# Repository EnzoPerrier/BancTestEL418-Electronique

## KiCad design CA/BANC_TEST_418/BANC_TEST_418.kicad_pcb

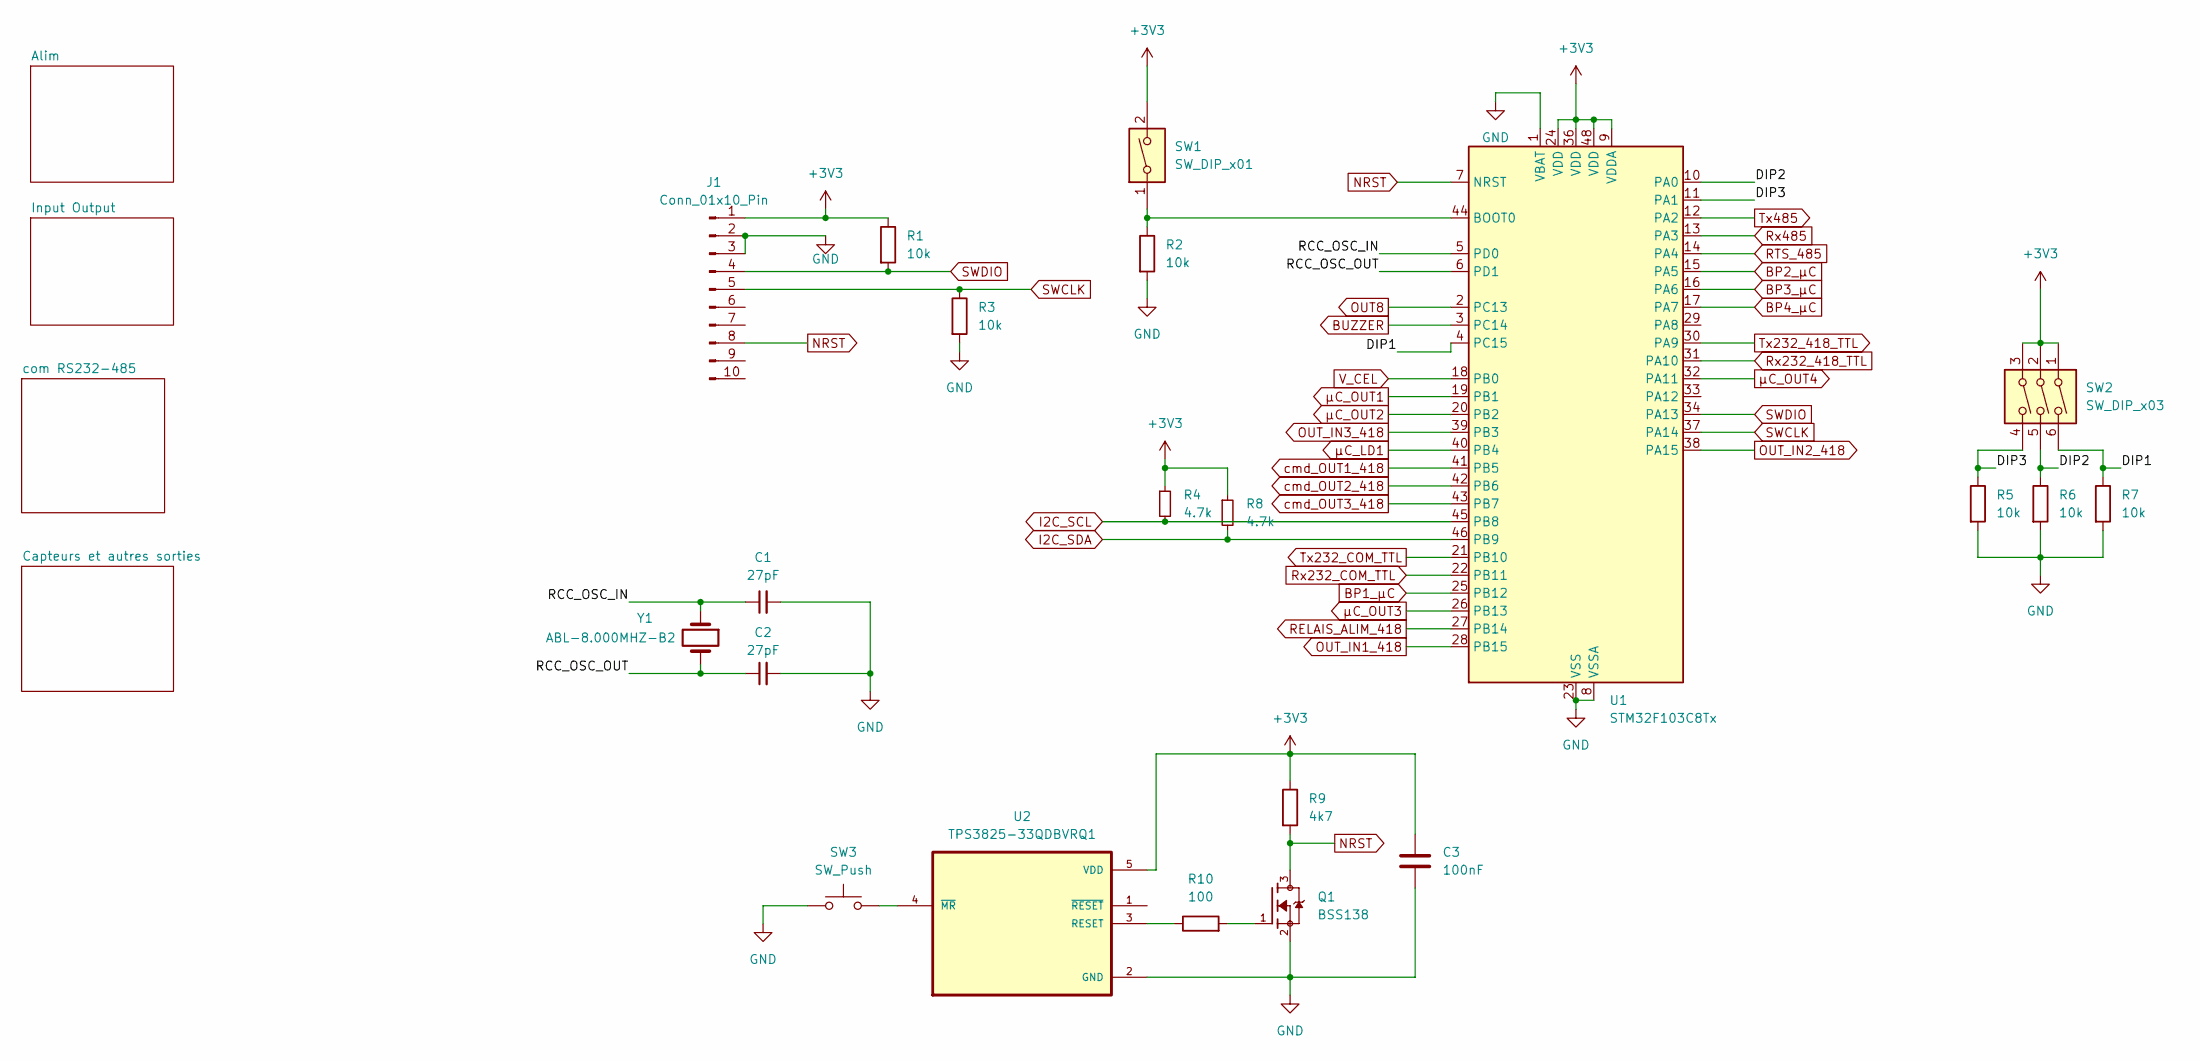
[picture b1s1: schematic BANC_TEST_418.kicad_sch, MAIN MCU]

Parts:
C1, C2: 27pF; C_0805_2012Metric_Pad1.18x1.45mm_HandSolder
C3: 100nF; C_0805_2012Metric_Pad1.18x1.45mm_HandSolder
J1: Conn_01x10_Pin; PinHeader_1x10_P2.54mm_Vertical
Q1: BSS138; SOT95P240X111-3N; PARTREV 30 Jan 2018
R1, R2, R3, R5, R6, R7: 10k; R_0805_2012Metric_Pad1.20x1.40mm_HandSolder
R4, R8: 4.7k; R_0805_2012Metric_Pad1.20x1.40mm_HandSolder
R9: 4k7; R_0805_2012Metric_Pad1.20x1.40mm_HandSolder
R10: 100; R_0805_2012Metric_Pad1.20x1.40mm_HandSolder
SW1: SW_DIP_x01; SW_DIP_SPSTx01_Slide_9.78x4.72mm_W8.61mm_P2.54mm
SW2: SW_DIP_x03; SW_DIP_SPSTx03_Slide_Omron_A6S-310x_W8.9mm_P2.54mm
SW3: SW_Push; SW_SPST_Omron_B3FS-100xP
U1: STM32F103C8Tx; LQFP-48_7x7mm_P0.5mm
U2: TPS3825-33QDBVRQ1; TPS3825-SOT95P280X145-5N
Y1: ABL-8.000MHZ-B2; Crystal_SMD_HC49-SD

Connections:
+3V3: C3.1, J1.1, R1.1, R4.1, R8.1, R9.1, SW1.2, SW2.1, SW2.2, SW2.3, U1.9 (VDDA), U1.24 (VDD), U1.36 (VDD), U1.48 (VDD), U2.5 (VDD); also elsewhere on the board
/DIP1: R7.1, SW2.6, U1.4 (PC15)
/DIP2: R6.1, SW2.5, U1.10 (PA0)
/DIP3: R5.1, SW2.4, U1.11 (PA1)
/RCC_OSC_IN: C1.1, U1.5 (PD0), Y1.1
/RCC_OSC_OUT: C2.1, U1.6 (PD1), Y1.2
BP1_µC: U1.25 (PB12); also elsewhere on the board
BP2_µC: U1.15 (PA5); also elsewhere on the board
BP3_µC: U1.16 (PA6); also elsewhere on the board
BP4_µC: U1.17 (PA7); also elsewhere on the board
BUZZER: U1.3 (PC14); also elsewhere on the board
GND: C1.2, C2.2, C3.2, J1.2, J1.3, Q1.2, R2.2, R3.2, R5.2, R6.2, R7.2, SW3.1, U1.1 (VBAT), U1.8 (VSSA), U1.23 (VSS), U1.35 (VSS), U1.47 (VSS), U2.2 (GND); also elsewhere on the board
I2C_SCL: R4.2, U1.45 (PB8); also elsewhere on the board
I2C_SDA: R8.2, U1.46 (PB9); also elsewhere on the board
NRST: J1.8, Q1.3, R9.2, U1.7 (NRST)
unnamed: Q1.1, R10.2
unnamed: R2.1, SW1.1, U1.44 (BOOT0)
unnamed: R10.1, U2.3 (RESET)
unnamed: SW3.2, U2.4 (~MR)
OUT8: U1.2 (PC13)
OUT_IN1_418: U1.28 (PB15); also elsewhere on the board
OUT_IN2_418: U1.38 (PA15); also elsewhere on the board
OUT_IN3_418: U1.39 (PB3); also elsewhere on the board
RELAIS_ALIM_418: U1.27 (PB14); also elsewhere on the board
RTS_485: U1.14 (PA4); also elsewhere on the board
Rx232_418_TTL: U1.31 (PA10); also elsewhere on the board
Rx232_COM_TTL: U1.22 (PB11); also elsewhere on the board
Rx485: U1.13 (PA3); also elsewhere on the board
SWCLK: J1.5, R3.1, U1.37 (PA14)
SWDIO: J1.4, R1.2, U1.34 (PA13)
Tx232_418_TTL: U1.30 (PA9); also elsewhere on the board
Tx232_COM_TTL: U1.21 (PB10); also elsewhere on the board
Tx485: U1.12 (PA2); also elsewhere on the board
V_CEL: U1.18 (PB0); also elsewhere on the board
cmd_OUT1_418: U1.41 (PB5); also elsewhere on the board
cmd_OUT2_418: U1.42 (PB6); also elsewhere on the board
cmd_OUT3_418: U1.43 (PB7); also elsewhere on the board
µC_LD1: U1.40 (PB4); also elsewhere on the board
µC_OUT1: U1.19 (PB1); also elsewhere on the board
µC_OUT2: U1.20 (PB2); also elsewhere on the board
µC_OUT3: U1.26 (PB13); also elsewhere on the board
µC_OUT4: U1.32 (PA11); also elsewhere on the board

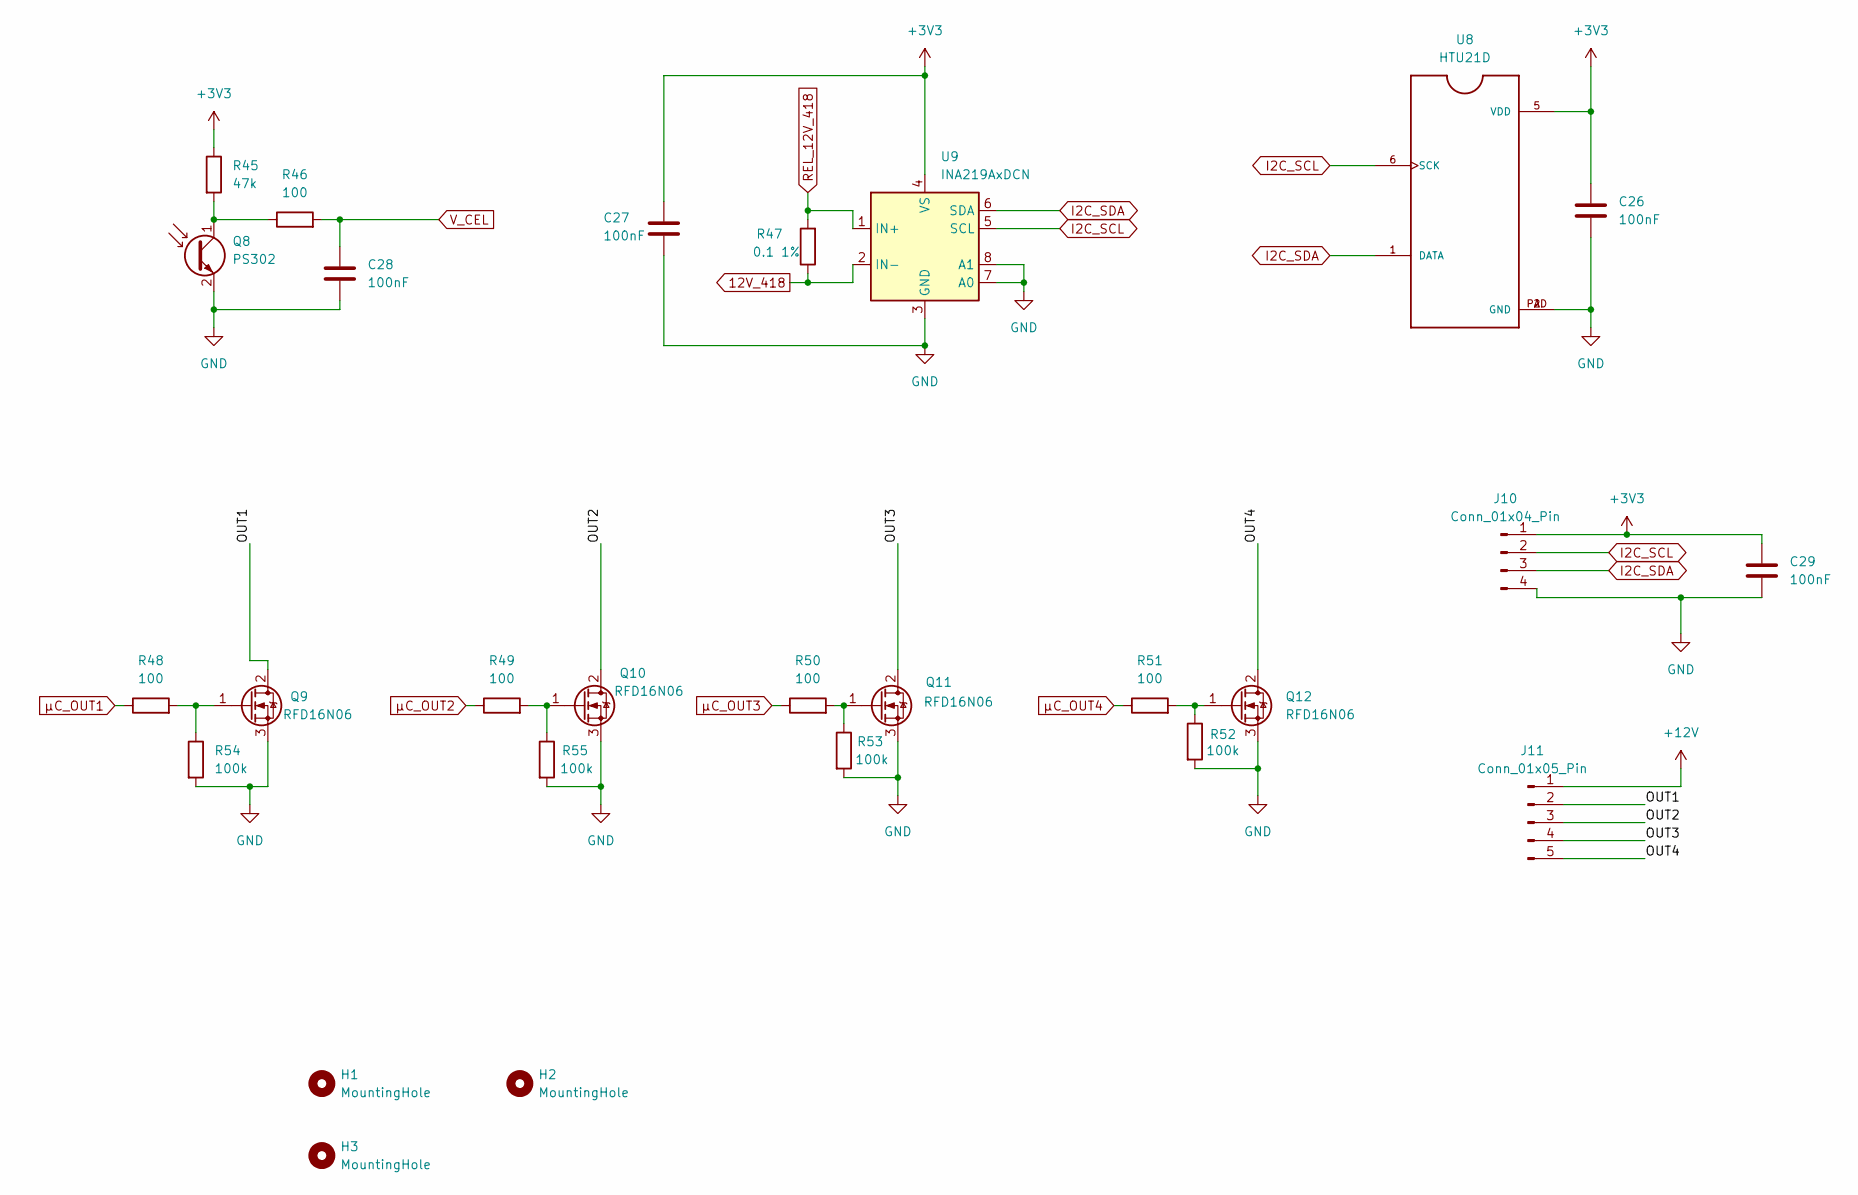
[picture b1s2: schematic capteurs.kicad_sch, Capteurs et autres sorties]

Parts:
C26, C27, C28, C29: 100nF; C_0805_2012Metric_Pad1.18x1.45mm_HandSolder
H1, H2, H3: MountingHole; MountingHole_4.3mm_M4_Pad
J10: Conn_01x04_Pin; NS-Tech_Grove_1x04_P2mm_Vertical
J11: Conn_01x05_Pin; PhoenixContact_MCV_1,5_5-G-3.81_1x05_P3.81mm_Vertical
Q8: PS302; LED_D5.0mm_Clear
Q9, Q10, Q11, Q12: RFD16N06; TO-252-2
R45: 47k; R_0805_2012Metric_Pad1.20x1.40mm_HandSolder
R46, R48, R49, R50, R51: 100; R_0805_2012Metric_Pad1.20x1.40mm_HandSolder
R47: 0.1 1%; R_2512_6332Metric_Pad1.40x3.35mm_HandSolder
R52, R53, R54, R55: 100k; R_0805_2012Metric_Pad1.20x1.40mm_HandSolder
U8: HTU21D; QFN100P300X300X100-7N
U9: INA219AxDCN; SOT-23-8

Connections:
12V_418: R47.1, U9.2 (IN-); also elsewhere on the board
+3V3: C26.1, C27.1, C29.1, J10.1, R45.1, U8.5 (VDD), U9.4 (VS); also elsewhere on the board
+12V: J11.1; also elsewhere on the board
/Capteurs et autres sorties/OUT1: J11.2, Q9.2 (D)
/Capteurs et autres sorties/OUT2: J11.3, Q10.2 (D)
/Capteurs et autres sorties/OUT3: J11.4, Q11.2 (D)
/Capteurs et autres sorties/OUT4: J11.5, Q12.2 (D)
GND: C26.2, C27.2, C28.2, C29.2, J10.4, Q8.2 (E), Q9.3 (S), Q10.3 (S), Q11.3 (S), Q12.3 (S), R52.2, R53.2, R54.2, R55.2, U8.2 (GND), U8.PAD (GND), U9.3 (GND), U9.7 (A0), U9.8 (A1); also elsewhere on the board
I2C_SCL: J10.2, U8.6 (SCK), U9.5 (SCL); also elsewhere on the board
I2C_SDA: J10.3, U8.1 (DATA), U9.6 (SDA); also elsewhere on the board
unnamed: Q8.1 (C), R45.2, R46.1
unnamed: Q9.1 (G), R48.2, R54.1
unnamed: Q10.1 (G), R49.2, R55.1
unnamed: Q11.1 (G), R50.2, R53.1
unnamed: Q12.1 (G), R51.2, R52.1
REL_12V_418: R47.2, U9.1 (IN+); also elsewhere on the board
V_CEL: C28.1, R46.2; also elsewhere on the board
µC_OUT1: R48.1; also elsewhere on the board
µC_OUT2: R49.1; also elsewhere on the board
µC_OUT3: R50.1; also elsewhere on the board
µC_OUT4: R51.1; also elsewhere on the board

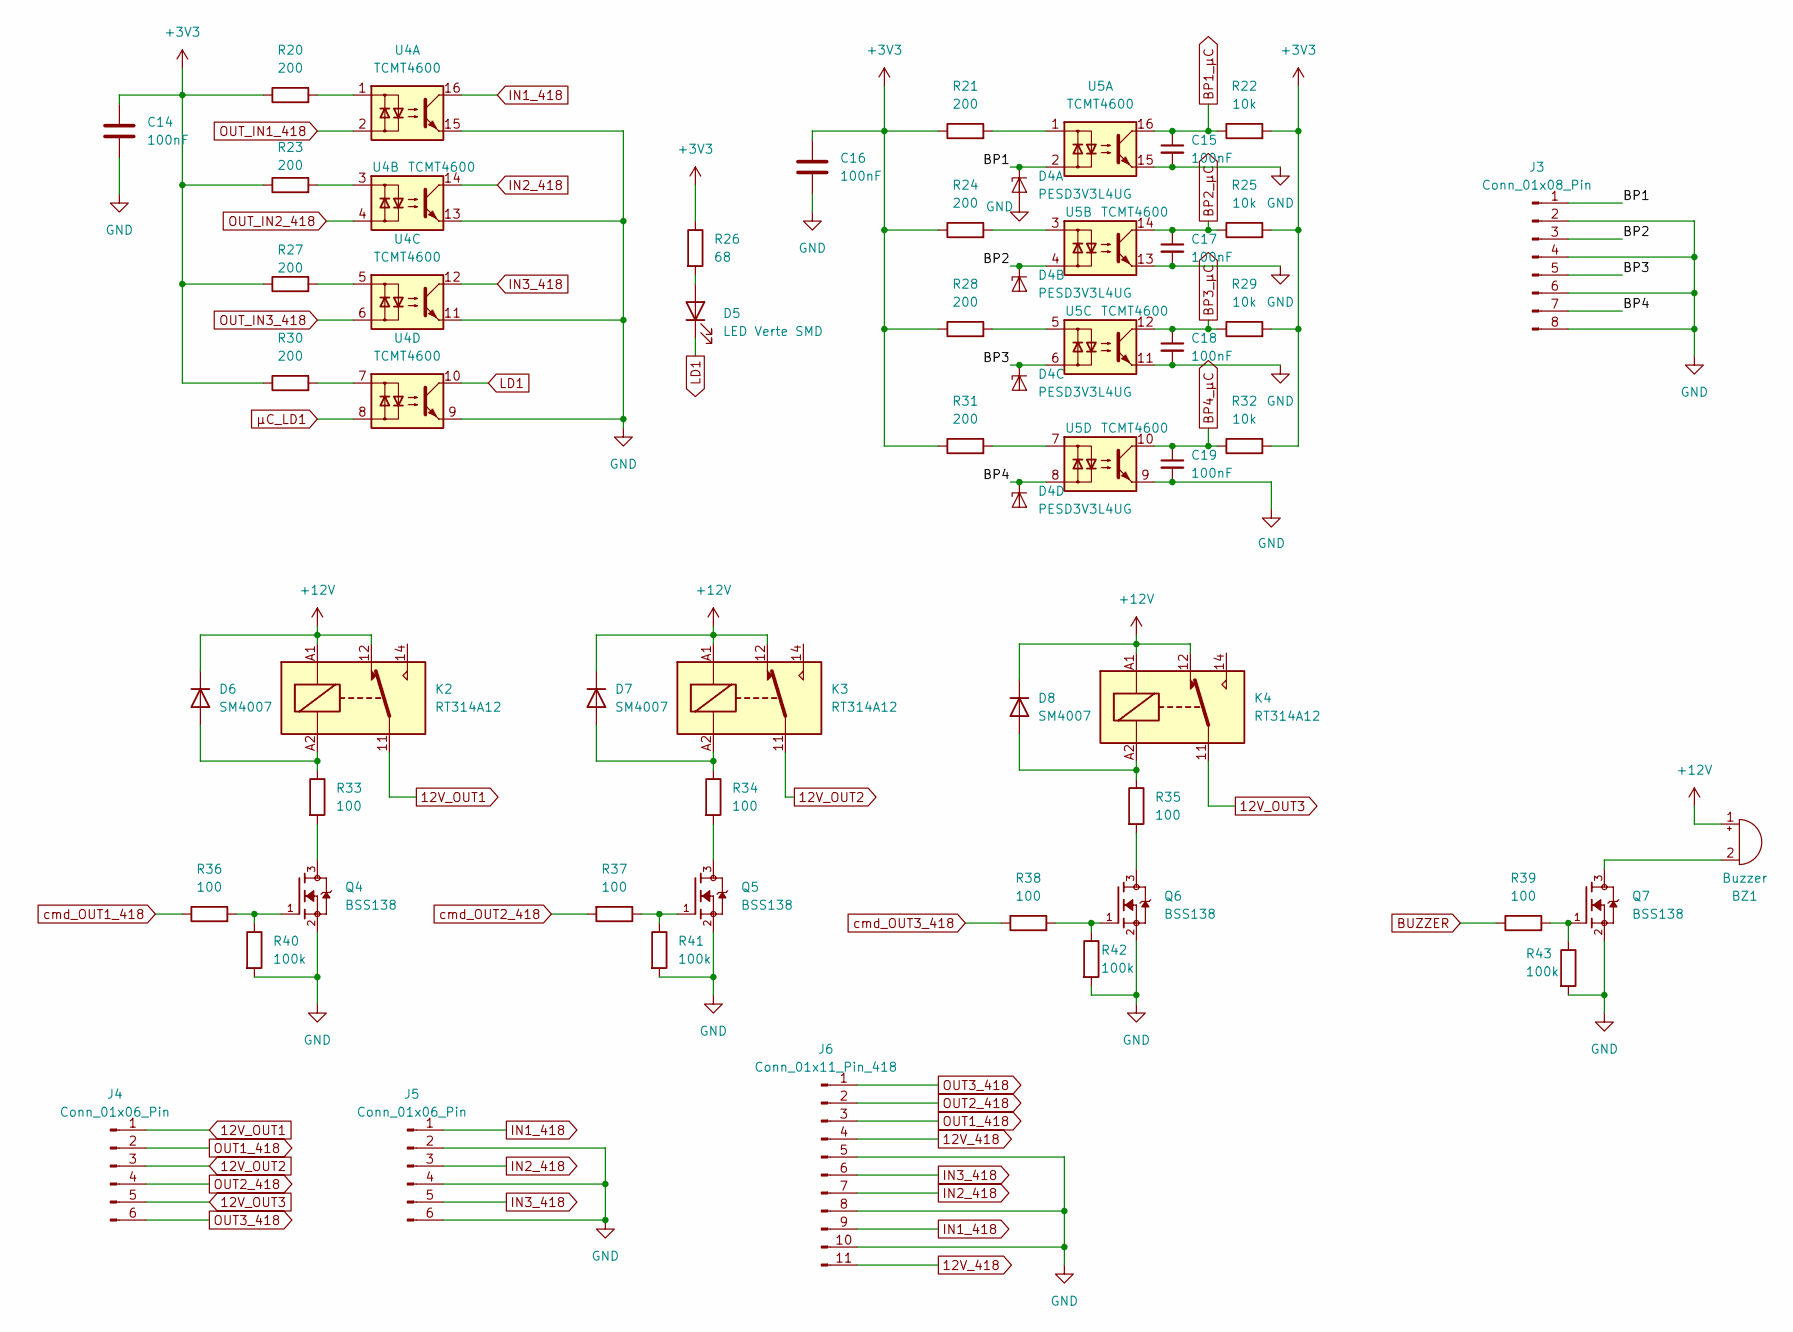
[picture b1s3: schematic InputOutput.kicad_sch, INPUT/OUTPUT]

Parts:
BZ1: Buzzer; Buzzer_15x7.5RM7.6
C14, C15, C16, C17, C18, C19: 100nF; C_0805_2012Metric_Pad1.18x1.45mm_HandSolder
D4: PESD3V3L4UG; SOT-353_SC-70-5
D5: LED Verte SMD; LED_0805_2012Metric_Pad1.15x1.40mm_HandSolder
D6, D7, D8: SM4007; D_MELF
J3: Conn_01x08_Pin; PhoenixContact_MCV_1,5_8-G-3.81_1x08_P3.81mm_Vertical
J4, J5: Conn_01x06_Pin; PhoenixContact_MCV_1,5_6-G-3.81_1x06_P3.81mm_Vertical
J6: Conn_01x11_Pin_418; PhoenixContact_MSTBVA_2,5_11-G-5,08_1x11_P5.08mm_Vertical
K2, K3, K4: RT314A12; Relay_SPDT_Schrack-RT1-16A-FormC_RM5mm
Q4, Q5, Q6, Q7: BSS138; SOT95P240X111-3N; PARTREV 30 Jan 2018
R20, R21, R23, R24, R27, R28, R30, R31: 200; R_0805_2012Metric_Pad1.20x1.40mm_HandSolder
R22, R25, R29, R32: 10k; R_0805_2012Metric_Pad1.20x1.40mm_HandSolder
R26: 68; R_0805_2012Metric_Pad1.20x1.40mm_HandSolder
R33, R34, R35, R36, R37, R38, R39: 100; R_0805_2012Metric_Pad1.20x1.40mm_HandSolder
R40, R41, R42, R43: 100k; R_0805_2012Metric_Pad1.20x1.40mm_HandSolder
U4, U5: TCMT4600; SOP-16_4.55x10.3mm_P1.27mm

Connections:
12V_418: J6.4, J6.11; also elsewhere on the board
12V_OUT1: J4.1, K2.11
12V_OUT2: J4.3, K3.11
12V_OUT3: J4.5, K4.11
+3V3: C14.1, C16.1, R20.1, R21.1, R22.2, R23.1, R24.1, R25.2, R26.1, R27.1, R28.1, R29.2, R30.1, R31.1, R32.2; also elsewhere on the board
+12V: BZ1.1 (+), D6.1 (K), D7.1 (K), D8.1 (K), K2.12, K2.A1, K3.12, K3.A1, K4.12, K4.A1; also elsewhere on the board
/Input Output/BP1: D4.1 (K1), J3.1, U5.2
/Input Output/BP2: D4.3 (K2), J3.3, U5.4
/Input Output/BP3: D4.4 (K3), J3.5, U5.6
/Input Output/BP4: D4.5 (K4), J3.7, U5.8
BP1_µC: C15.1, R22.1, U5.16; also elsewhere on the board
BP2_µC: C17.1, R25.1, U5.14; also elsewhere on the board
BP3_µC: C18.1, R29.1, U5.12; also elsewhere on the board
BP4_µC: C19.1, R32.1, U5.10; also elsewhere on the board
BUZZER: R39.1; also elsewhere on the board
GND: C14.2, C15.2, C16.2, C17.2, C18.2, C19.2, D4.2 (A), J3.2, J3.4, J3.6, J3.8, J5.2, J5.4, J5.6, J6.5, J6.8, J6.10, Q4.2, Q5.2, Q6.2, Q7.2, R40.2, R41.2, R42.2, R43.2, U4.9, U4.11, U4.13, U4.15, U5.9, U5.11, U5.13, U5.15; also elsewhere on the board
IN1_418: J5.1, J6.9, U4.16
IN2_418: J5.3, J6.7, U4.14
IN3_418: J5.5, J6.6, U4.12
LD1: D5.1 (K), U4.10
unnamed: BZ1.2 (-), Q7.3
unnamed: D5.2 (A), R26.2
unnamed: D6.2 (A), K2.A2, R33.1
unnamed: D7.2 (A), K3.A2, R34.1
unnamed: D8.2 (A), K4.A2, R35.1
unnamed: Q4.1, R36.2, R40.1
unnamed: Q4.3, R33.2
unnamed: Q5.1, R37.1, R41.1
unnamed: Q5.3, R34.2
unnamed: Q6.1, R38.2, R42.1
unnamed: Q6.3, R35.2
unnamed: Q7.1, R39.2, R43.1
unnamed: R20.2, U4.1
unnamed: R21.2, U5.1
unnamed: R23.2, U4.3
unnamed: R24.2, U5.3
unnamed: R27.2, U4.5
unnamed: R28.2, U5.5
unnamed: R30.2, U4.7
unnamed: R31.2, U5.7
OUT1_418: J4.2, J6.3
OUT2_418: J4.4, J6.2
OUT3_418: J4.6, J6.1
OUT_IN1_418: U4.2; also elsewhere on the board
OUT_IN2_418: U4.4; also elsewhere on the board
OUT_IN3_418: U4.6; also elsewhere on the board
cmd_OUT1_418: R36.1; also elsewhere on the board
cmd_OUT2_418: R37.2; also elsewhere on the board
cmd_OUT3_418: R38.1; also elsewhere on the board
µC_LD1: U4.8; also elsewhere on the board

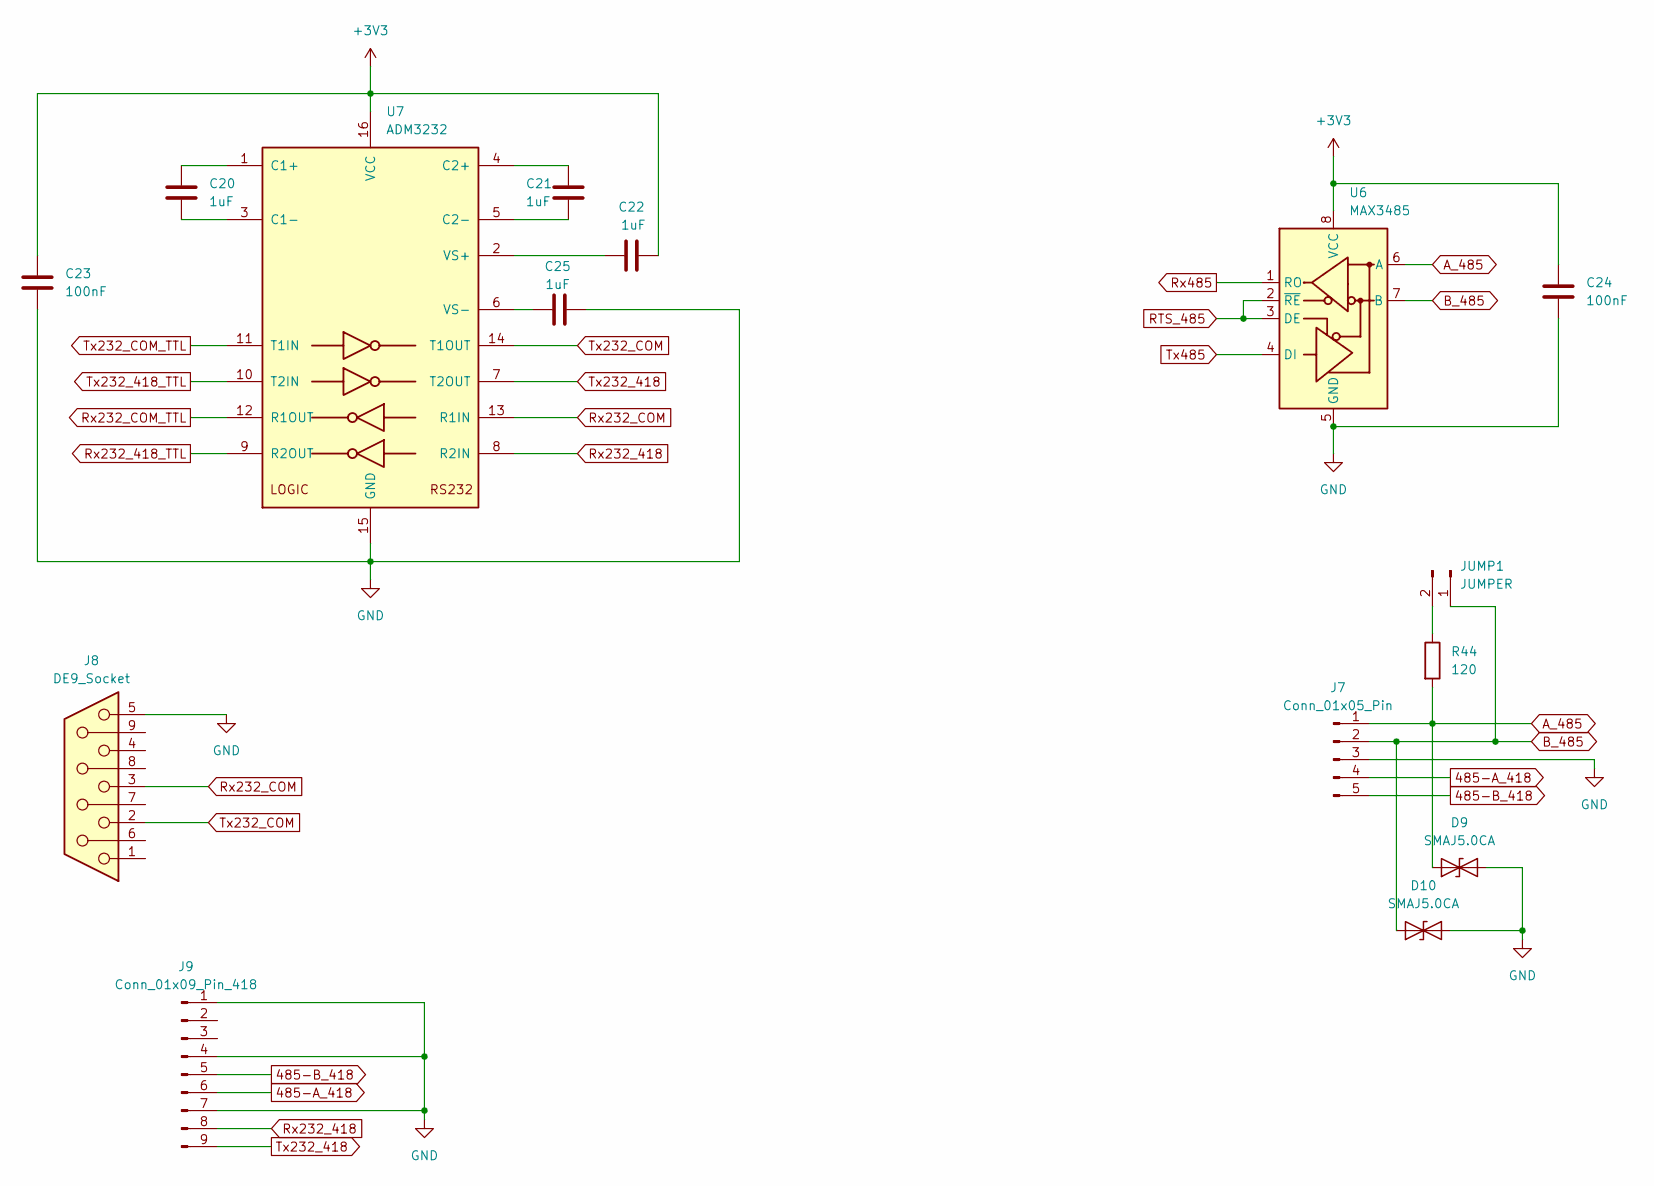
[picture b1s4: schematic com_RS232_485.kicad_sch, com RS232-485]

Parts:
C20, C21, C22, C25: 1uF; C_0805_2012Metric_Pad1.18x1.45mm_HandSolder
C23, C24: 100nF; C_0805_2012Metric_Pad1.18x1.45mm_HandSolder
D9, D10: SMAJ5.0CA; D_SMA
J7: Conn_01x05_Pin; PhoenixContact_MCV_1,5_5-G-3.81_1x05_P3.81mm_Vertical
J8: DE9_Socket; DSUB-9_Socket_Horizontal_P2.77x2.84mm_EdgePinOffset7.70mm_H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
J9: Conn_01x09_Pin_418; PhoenixContact_MCV_1,5_9-G-3.81_1x09_P3.81mm_Vertical
JUMP1: JUMPER; PinHeader_1x02_P2.54mm_Vertical
R44: 120; R_0805_2012Metric_Pad1.20x1.40mm_HandSolder
U6: MAX3485; SOIC-8_3.9x4.9mm_P1.27mm
U7: ADM3232; SOP-16_4.4x10.4mm_P1.27mm

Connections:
485-A_418: J7.4, J9.6
485-B_418: J7.5, J9.5
+3V3: C22.2, C23.1, C24.1, U6.8 (VCC), U7.16 (VCC); also elsewhere on the board
A_485: D9.1 (A1), J7.1, R44.2, U6.6 (A)
B_485: D10.1 (A1), J7.2, JUMP1.1, U6.7 (B)
GND: C23.2, C24.2, C25.2, D9.2 (A2), D10.2 (A2), J7.3, J8.5, J9.1, J9.4, J9.7, U6.5 (GND), U7.15 (GND); also elsewhere on the board
unnamed: JUMP1.2, R44.1
unnamed: C20.1, U7.1 (C1+)
unnamed: C20.2, U7.3 (C1-)
unnamed: C21.1, U7.4 (C2+)
unnamed: C21.2, U7.5 (C2-)
unnamed: C22.1, U7.2 (VS+)
unnamed: C25.1, U7.6 (VS-)
RTS_485: U6.2 (~RE), U6.3 (DE); also elsewhere on the board
Rx232_418: J9.8, U7.8 (R2IN)
Rx232_418_TTL: U7.9 (R2OUT); also elsewhere on the board
Rx232_COM: J8.3, U7.13 (R1IN)
Rx232_COM_TTL: U7.12 (R1OUT); also elsewhere on the board
Rx485: U6.1 (RO); also elsewhere on the board
Tx232_418: J9.9, U7.7 (T2OUT)
Tx232_418_TTL: U7.10 (T2IN); also elsewhere on the board
Tx232_COM: J8.2, U7.14 (T1OUT)
Tx232_COM_TTL: U7.11 (T1IN); also elsewhere on the board
Tx485: U6.4 (DI); also elsewhere on the board

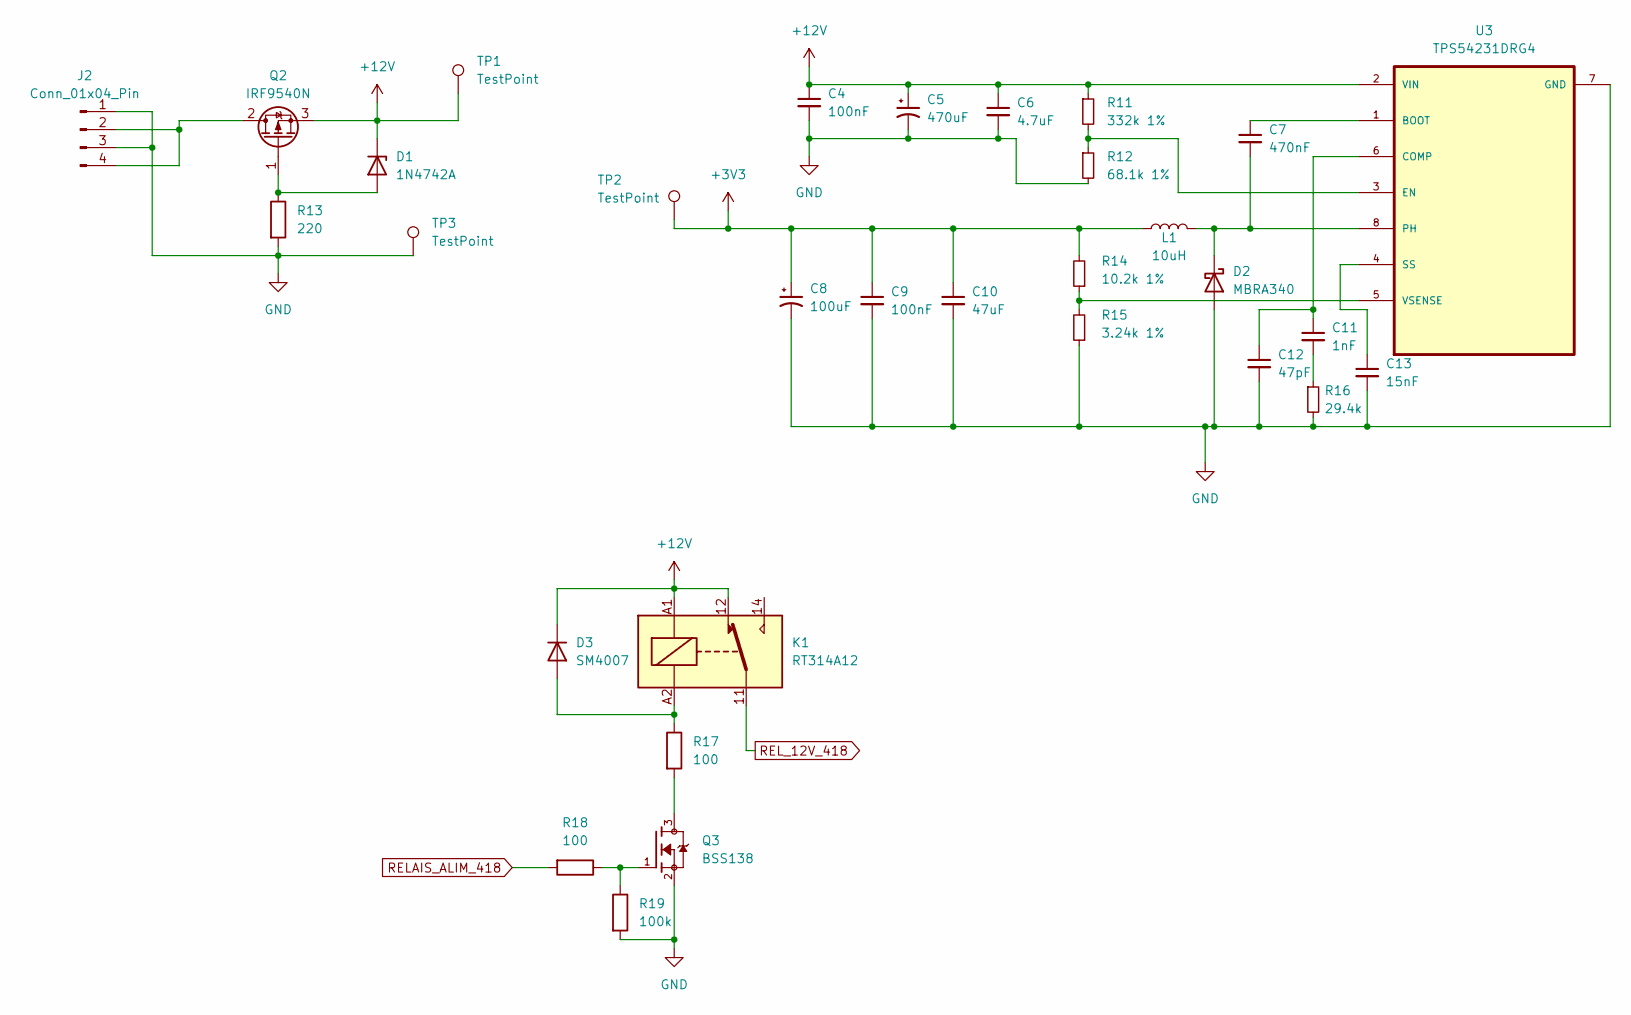
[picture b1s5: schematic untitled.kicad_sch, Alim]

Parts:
C4, C9: 100nF; C_0805_2012Metric_Pad1.18x1.45mm_HandSolder
C5: 470uF; C_Elec_10x10.2
C6: 4.7uF; C_1210_3225Metric_Pad1.33x2.70mm_HandSolder
C7: 470nF; C_0805_2012Metric_Pad1.18x1.45mm_HandSolder
C8: 100uF; CP_Elec_6.3x9.9
C10: 47uF; C_1210_3225Metric_Pad1.33x2.70mm_HandSolder
C11: 1nF; C_0805_2012Metric_Pad1.18x1.45mm_HandSolder
C12: 47pF; C_0805_2012Metric_Pad1.18x1.45mm_HandSolder
C13: 15nF; C_0805_2012Metric_Pad1.18x1.45mm_HandSolder
D1: 1N4742A; D_DO-41_SOD81_P10.16mm_Horizontal
D2: MBRA340; D_SMA
D3: SM4007; D_MELF
J2: Conn_01x04_Pin; PhoenixContact_MCV_1,5_4-G-3.81_1x04_P3.81mm_Vertical
K1: RT314A12; Relay_SPDT_Schrack-RT1-16A-FormC_RM5mm
L1: 10uH; L_Coilcraft_MOS6020-XXX
Q2: IRF9540N; TO-252-2
Q3: BSS138; SOT95P240X111-3N; PARTREV 30 Jan 2018
R11: 332k 1%; R_0805_2012Metric_Pad1.20x1.40mm_HandSolder
R12: 68.1k 1%; R_0805_2012Metric_Pad1.20x1.40mm_HandSolder
R13: 220; R_0805_2012Metric_Pad1.20x1.40mm_HandSolder
R14: 10.2k 1%; R_0805_2012Metric_Pad1.20x1.40mm_HandSolder
R15: 3.24k 1%; R_0805_2012Metric_Pad1.20x1.40mm_HandSolder
R16: 29.4k; R_0805_2012Metric_Pad1.20x1.40mm_HandSolder
R17, R18: 100; R_0805_2012Metric_Pad1.20x1.40mm_HandSolder
R19: 100k; R_0805_2012Metric_Pad1.20x1.40mm_HandSolder
TP1, TP2: TestPoint; TestPoint_Pad_1.5x1.5mm
TP3: TestPoint; TestPoint_Loop_D2.50mm_Drill1.85mm
U3: TPS54231DRG4; SOIC127P599X175-8N; DigiKey_Part_Number 296-52801-2-ND

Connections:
+3V3: C8.1, C9.1, C10.1, L1.1, R14.2, TP2.1; also elsewhere on the board
+12V: C4.1, C5.1, C6.1, D1.1 (K), D3.1 (K), K1.12, K1.A1, Q2.3 (S), R11.1, TP1.1, U3.2 (VIN); also elsewhere on the board
GND: C4.2, C5.2, C6.2, C8.2, C9.2, C10.2, C12.2, C13.2, D2.2 (A), J2.1, J2.3, Q3.2, R12.2, R13.2, R15.1, R16.2, R19.2, TP3.1, U3.7 (GND); also elsewhere on the board
unnamed: C11.2, R16.1
unnamed: D1.2 (A), Q2.1 (G), R13.1
unnamed: C7.2, D2.1 (K), L1.2, U3.8 (PH)
unnamed: D3.2 (A), K1.A2, R17.1
unnamed: J2.2, J2.4, Q2.2 (D)
unnamed: Q3.1, R18.1, R19.1
unnamed: Q3.3, R17.2
unnamed: C7.1, U3.1 (BOOT)
unnamed: C11.1, C12.1, U3.6 (COMP)
unnamed: R11.2, R12.1, U3.3 (EN)
unnamed: C13.1, U3.4 (SS)
unnamed: R14.1, R15.2, U3.5 (VSENSE)
RELAIS_ALIM_418: R18.2; also elsewhere on the board
REL_12V_418: K1.11; also elsewhere on the board

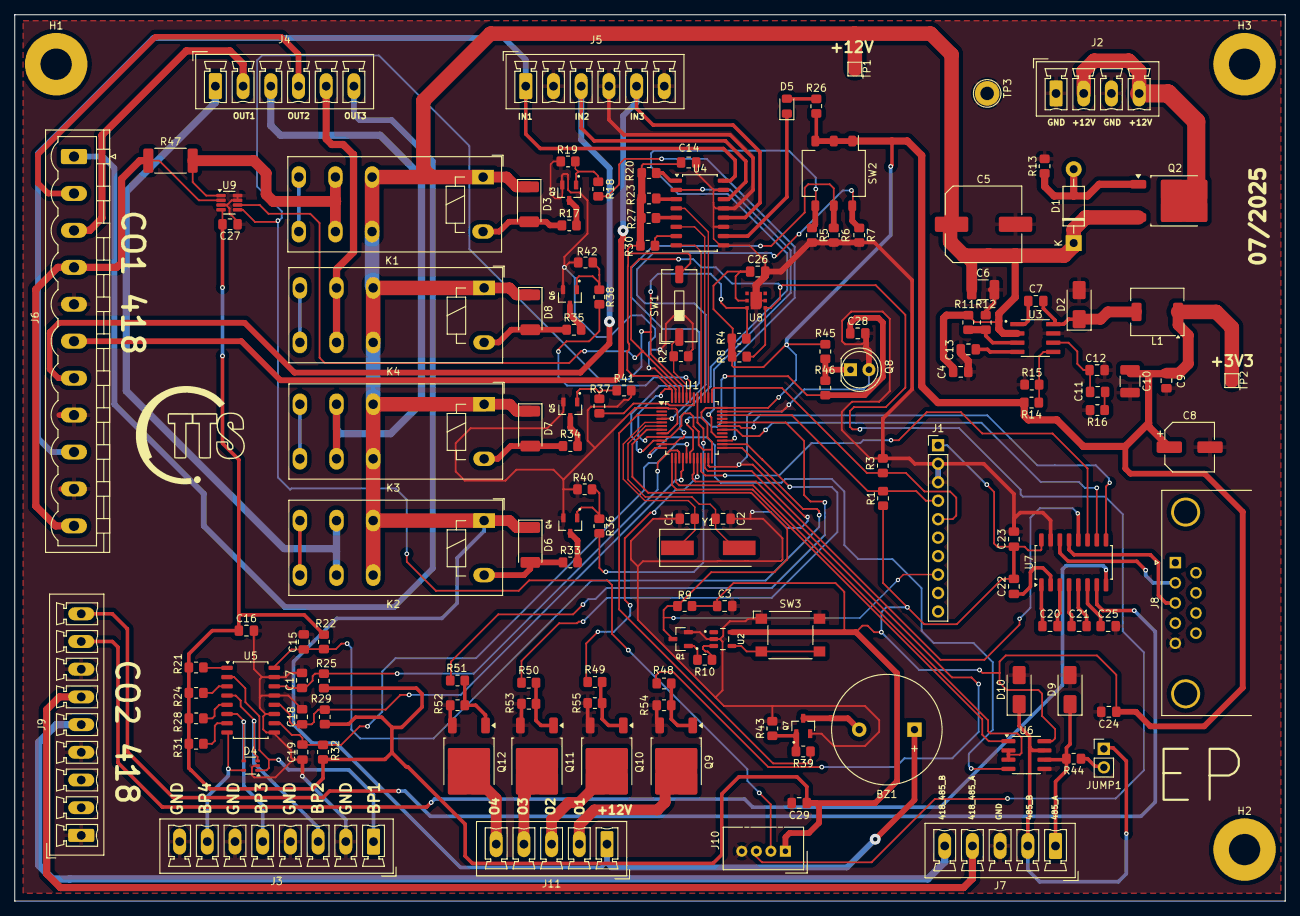
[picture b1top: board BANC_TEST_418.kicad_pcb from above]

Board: 2 copper layers, 174.8 x 121.9 mm, 143 parts (0 on the bottom side), 114 nets.

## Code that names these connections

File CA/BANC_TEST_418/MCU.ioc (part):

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Mcu.Name=STM32F103C(8-B)Tx
Mcu.Package=LQFP48
Mcu.UserName=STM32F103C8Tx
PA0-WKUP.GPIOParameters=GPIO_Label
PA0-WKUP.GPIO_Label=DIP2
PA0-WKUP.Signal=GPIO_Input
PA1.GPIOParameters=GPIO_Label
PA1.GPIO_Label=DIP3
PA1.Signal=GPIO_Input
PA10.GPIOParameters=GPIO_Label
PA10.GPIO_Label=Rx232
PA10.Mode=Asynchronous
PA10.Signal=USART1_RX
PA11.GPIOParameters=GPIO_Label
PA11.GPIO_Label=OUT4
PA11.Signal=GPIO_Output
PA13.GPIOParameters=GPIO_Label
PA13.GPIO_Label=SWDIO
PA13.Mode=Serial_Wire
PA13.Signal=SYS_JTMS-SWDIO
PA14.GPIOParameters=GPIO_Label
PA14.GPIO_Label=SWCLK
PA14.Mode=Serial_Wire
PA14.Signal=SYS_JTCK-SWCLK
PA15.GPIOParameters=GPIO_Label
PA15.GPIO_Label=OUT_IN2_418
PA15.Signal=GPIO_Output
PA2.GPIOParameters=GPIO_Label
PA2.GPIO_Label=Tx485
PA2.Mode=Asynchronous
PA2.Signal=USART2_TX
PA3.GPIOParameters=GPIO_Label
PA3.GPIO_Label=Rx485
PA3.Mode=Asynchronous
PA3.Signal=USART2_RX
PA4.GPIOParameters=GPIO_Label
PA4.GPIO_Label=RTS_485
PA4.Signal=GPIO_Output
PA5.GPIOParameters=GPIO_Label
PA5.GPIO_Label=BP2
PA5.Signal=GPIO_Input
PA6.GPIOParameters=GPIO_Label
PA6.GPIO_Label=BP3
PA6.Signal=GPIO_Input
PA7.GPIOParameters=GPIO_Label
PA7.GPIO_Label=BP4
PA7.Signal=GPIO_Input
PA9.GPIOParameters=GPIO_Label
PA9.GPIO_Label=Tx232
PA9.Mode=Asynchronous
PA9.Signal=USART1_TX
PB0.GPIOParameters=GPIO_Label
PB0.GPIO_Label=V_CEL
PB0.Signal=SharedAnalog_PB0
PB1.GPIOParameters=GPIO_Label
PB1.GPIO_Label=OUT1
PB1.Signal=GPIO_Output
PB10.GPIOParameters=GPIO_Speed,GPIO_Mode
PB10.GPIO_Mode=GPIO_MODE_AF_PP
PB10.GPIO_Speed=GPIO_SPEED_FREQ_HIGH
PB10.Mode=Asynchronous
PB10.Signal=USART3_TX
PB11.GPIOParameters=GPIO_PuPd,GPIO_Mode
PB11.GPIO_Mode=GPIO_MODE_INPUT
PB11.GPIO_PuPd=GPIO_NOPULL
PB11.Mode=Asynchronous
PB11.Signal=USART3_RX
PB12.GPIOParameters=GPIO_Label
PB12.GPIO_Label=BP1_IRQ
PB12.Signal=GPXTI12
PB13.GPIOParameters=GPIO_Label
PB13.GPIO_Label=OUT3
PB13.Signal=GPIO_Output
PB14.GPIOParameters=GPIO_Label
PB14.GPIO_Label=RELAIS_ALIM_418
PB14.Signal=GPIO_Output
PB15.GPIOParameters=GPIO_Label
PB15.GPIO_Label=OUT_IN1_418
PB15.Signal=GPIO_Output
PB2.GPIOParameters=GPIO_Label
PB2.GPIO_Label=OUT2
PB2.Signal=GPIO_Output
PB3.GPIOParameters=GPIO_Label
PB3.GPIO_Label=OUT_IN3_418
PB3.Signal=GPIO_Output
PB4.GPIOParameters=GPIO_Label
PB4.GPIO_Label=uC_LD1
PB4.Signal=GPIO_Output
PB5.GPIOParameters=GPIO_Label
PB5.GPIO_Label=cmd_OUT1_418
PB5.Signal=GPIO_Output
PB6.GPIOParameters=GPIO_Label
PB6.GPIO_Label=cmd_OUT2_418
PB6.Signal=GPIO_Output
PB7.GPIOParameters=GPIO_Label
PB7.GPIO_Label=cmd_OUT3_418
PB7.Signal=GPIO_Output
PB8.GPIOParameters=GPIO_Label
PB8.GPIO_Label=I2C_SCL
PB8.Mode=I2C
PB8.Signal=I2C1_SCL
PB9.GPIOParameters=GPIO_Label
PB9.GPIO_Label=I2C_SDA
PB9.Mode=I2C
PB9.Signal=I2C1_SDA
PC13-TAMPER-RTC.GPIOParameters=GPIO_Label
PC13-TAMPER-RTC.GPIO_Label=OUT8
PC13-TAMPER-RTC.Signal=GPIO_Output
PC14-OSC32_IN.GPIOParameters=GPIO_Label
PC14-OSC32_IN.GPIO_Label=BUZZER
PC14-OSC32_IN.Signal=GPIO_Output
PC15-OSC32_OUT.GPIOParameters=GPIO_Label
PC15-OSC32_OUT.GPIO_Label=DIP1
PC15-OSC32_OUT.Signal=GPIO_Input
PD0-OSC_IN.Mode=HSE-External-Oscillator
PD0-OSC_IN.Signal=RCC_OSC_IN
PD1-OSC_OUT.Mode=HSE-External-Oscillator
PD1-OSC_OUT.Signal=RCC_OSC_OUT
RCC.SYSCLKFreq_VALUE=72000000
RCC.SYSCLKSource=RCC_SYSCLKSOURCE_PLLCLK
board=custom

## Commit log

2025-11-05 modif doc
2025-11-06 Modif documentations
2025-11-06 modif doc 2
2025-11-06 modif doc 3
